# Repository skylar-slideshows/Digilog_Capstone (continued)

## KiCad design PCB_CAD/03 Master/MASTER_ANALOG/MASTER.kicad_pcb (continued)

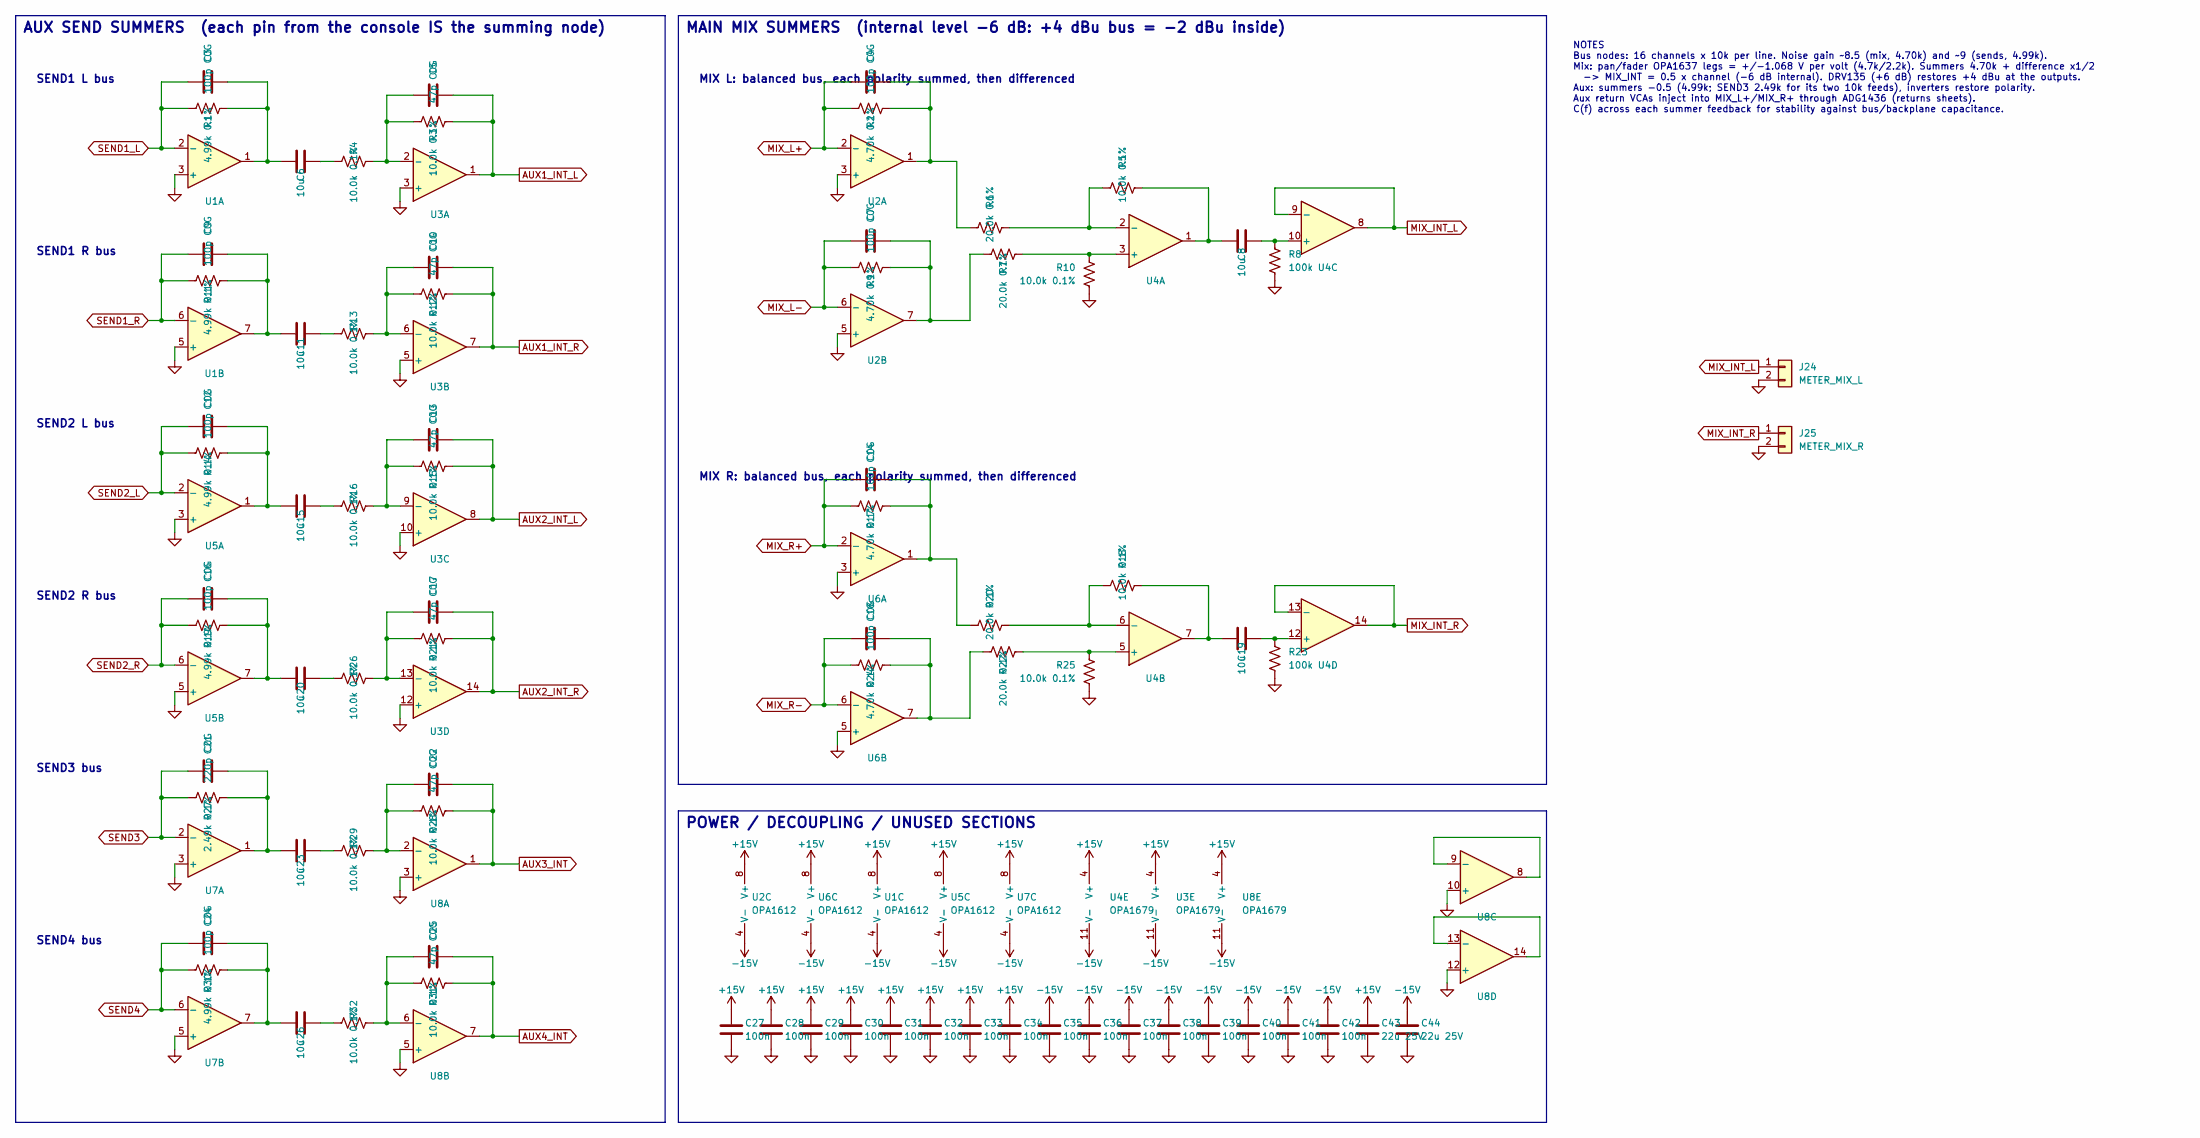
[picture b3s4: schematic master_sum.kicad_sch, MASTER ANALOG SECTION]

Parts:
C3, C4, C7, C9, C12, C14, C16, C18, C24: 100p C0G; C_0603_1608Metric; LCSC C14665
C5, C10, C13, C17, C22, C25: 47p C0G; C_0603_1608Metric; LCSC C105622
C6, C8, C11, C15, C19, C20, C23, C26: 10u; CP_Elec_6.3x5.4_Nichicon; LCSC C340735
C21: 220p C0G; C_0603_1608Metric; LCSC C694226
C27, C28, C29, C30, C31, C32, C33, C34, C35, C36, C37, C38, C39, C40, C41, C42: 100n; C_0603_1608Metric; LCSC C1590
C43, C44: 22u 25V; C_1210_3225Metric; LCSC C21397
J24: METER_MIX_L; PinHeader_1x02_P2.54mm_Vertical; LCSC dnp
J25: METER_MIX_R; PinHeader_1x02_P2.54mm_Vertical; LCSC dnp
R1, R11, R14, R19, R30: 4.99k 0.1%; R_0603_1608Metric; LCSC C190614
R2, R9, R17, R24: 4.70k 0.1%; R_0603_1608Metric; LCSC C328429
R3, R4, R5, R10, R12, R13, R15, R16, R18, R21, R25, R26, R28, R29, R31, R32: 10.0k 0.1%; R_0603_1608Metric; LCSC C95204
R6, R7, R20, R22: 20.0k 0.1%; R_0603_1608Metric; LCSC C190611
R8, R23: 100k; R_0603_1608Metric; LCSC C122538
R27: 2.49k 0.1%; R_0603_1608Metric; LCSC C319797
U1, U2, U5, U6, U7: OPA1612; SOIC-8_3.9x4.9mm_P1.27mm; LCSC C94590
U3, U4, U8: OPA1679; TSSOP-14_4.4x5mm_P0.65mm; LCSC C2057264

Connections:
+15V: C27.1, C28.1, C29.1, C30.1, C31.1, C32.1, C33.1, C34.1, C43.1, U1.8 (V+), U2.8 (V+), U3.4 (V+), U4.4 (V+), U5.8 (V+), U6.8 (V+), U7.8 (V+), U8.4 (V+); also elsewhere on the board
-15V: C35.1, C36.1, C37.1, C38.1, C39.1, C40.1, C41.1, C42.1, C44.1, U1.4 (V-), U2.4 (V-), U3.11 (V-), U4.11 (V-), U5.4 (V-), U6.4 (V-), U7.4 (V-), U8.11 (V-); also elsewhere on the board
AUX1_INT_L: C5.2, R3.2, U3.1; also elsewhere on the board
AUX1_INT_R: C10.2, R12.2, U3.7; also elsewhere on the board
AUX2_INT_L: C13.2, R15.2, U3.8; also elsewhere on the board
AUX2_INT_R: C17.2, R21.2, U3.14; also elsewhere on the board
AUX3_INT: C22.2, R28.2, U8.1; also elsewhere on the board
AUX4_INT: C25.2, R31.2, U8.7; also elsewhere on the board
GND: C27.2, C28.2, C29.2, C30.2, C31.2, C32.2, C33.2, C34.2, C35.2, C36.2, C37.2, C38.2, C39.2, C40.2, C41.2, C42.2, C43.2, C44.2, J24.2, J25.2, R8.2, R10.2, R23.2, R25.2, U1.3 (+), U1.5 (+), U2.3 (+), U2.5 (+), U3.3 (+), U3.5 (+), U3.10 (+), U3.12 (+), U5.3 (+), U5.5 (+), U6.3 (+), U6.5 (+), U7.3 (+), U7.5 (+), U8.3 (+), U8.5 (+), U8.10 (+), U8.12 (+); also elsewhere on the board
MIX_INT_L: J24.1, U4.8, U4.9 (-); also elsewhere on the board
MIX_INT_R: J25.1, U4.13 (-), U4.14; also elsewhere on the board
MIX_L+: C4.1, R2.1, U2.2 (-); also elsewhere on the board
MIX_L-: C7.1, R9.1, U2.6 (-); also elsewhere on the board
MIX_R+: C14.1, R17.1, U6.2 (-); also elsewhere on the board
MIX_R-: C18.1, R24.1, U6.6 (-); also elsewhere on the board
unnamed: C3.2, C6.1, R1.2, U1.1
unnamed: C4.2, R2.2, R6.1, U2.1
unnamed: C6.2, R4.1
unnamed: C7.2, R7.1, R9.2, U2.7
unnamed: C8.1, R5.2, U4.1
unnamed: C9.2, C11.1, R11.2, U1.7
unnamed: C11.2, R13.1
unnamed: C12.2, C15.1, R14.2, U5.1
unnamed: C14.2, R17.2, R20.1, U6.1
unnamed: C15.2, R16.1
unnamed: C16.2, C20.1, R19.2, U5.7
unnamed: C18.2, R22.1, R24.2, U6.7
unnamed: C19.1, R18.2, U4.7
unnamed: C20.2, R26.1
unnamed: C21.2, C23.1, R27.2, U7.1
unnamed: C23.2, R29.1
unnamed: C24.2, C26.1, R30.2, U7.7
unnamed: C26.2, R32.1
unnamed: C5.1, R3.1, R4.2, U3.2 (-)
unnamed: C10.1, R12.1, R13.2, U3.6 (-)
unnamed: C13.1, R15.1, R16.2, U3.9 (-)
unnamed: C17.1, R21.1, R26.2, U3.13 (-)
unnamed: R7.2, R10.1, U4.3 (+)
unnamed: R5.1, R6.2, U4.2 (-)
unnamed: R22.2, R25.1, U4.5 (+)
unnamed: R18.1, R20.2, U4.6 (-)
unnamed: C8.2, R8.1, U4.10 (+)
unnamed: C19.2, R23.1, U4.12 (+)
unnamed: C22.1, R28.1, R29.2, U8.2 (-)
unnamed: C25.1, R31.1, R32.2, U8.6 (-)
unnamed: U8.8, U8.9 (-)
unnamed: U8.13 (-), U8.14
SEND1_L: C3.1, R1.1, U1.2 (-); also elsewhere on the board
SEND1_R: C9.1, R11.1, U1.6 (-); also elsewhere on the board
SEND2_L: C12.1, R14.1, U5.2 (-); also elsewhere on the board
SEND2_R: C16.1, R19.1, U5.6 (-); also elsewhere on the board
SEND3: C21.1, R27.1, U7.2 (-); also elsewhere on the board
SEND4: C24.1, R30.1, U7.6 (-); also elsewhere on the board

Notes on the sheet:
SEND3 bus
SEND2 R bus
SEND1 L bus
MIX L: balanced bus, each polarity summed, then differenced
SEND1 R bus
MAIN MIX SUMMERS (internal level -6 dB: +4 dBu bus = -2 dBu inside)
NOTES Bus nodes: 16 channels x 10k per line. Noise gain ~8.5 (mix, 4.70k) and ~9 (sends, 4.99k). Mix: pan/fader OPA1637 legs = +/-1.068 V per volt (4.7k/2.2k). Summers 4.70k + difference x1/2 -> MIX_INT = 0.5 x channel (-6 dB internal). DRV135 (+6 dB) restores +4 dBu at the outputs. Aux: summers -0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
SEND4 bus
AUX SEND SUMMERS (each pin from the console IS the summing node)
MIX R: balanced bus, each polarity summed, then differenced
SEND2 L bus
POWER / DECOUPLING / UNUSED SECTIONS

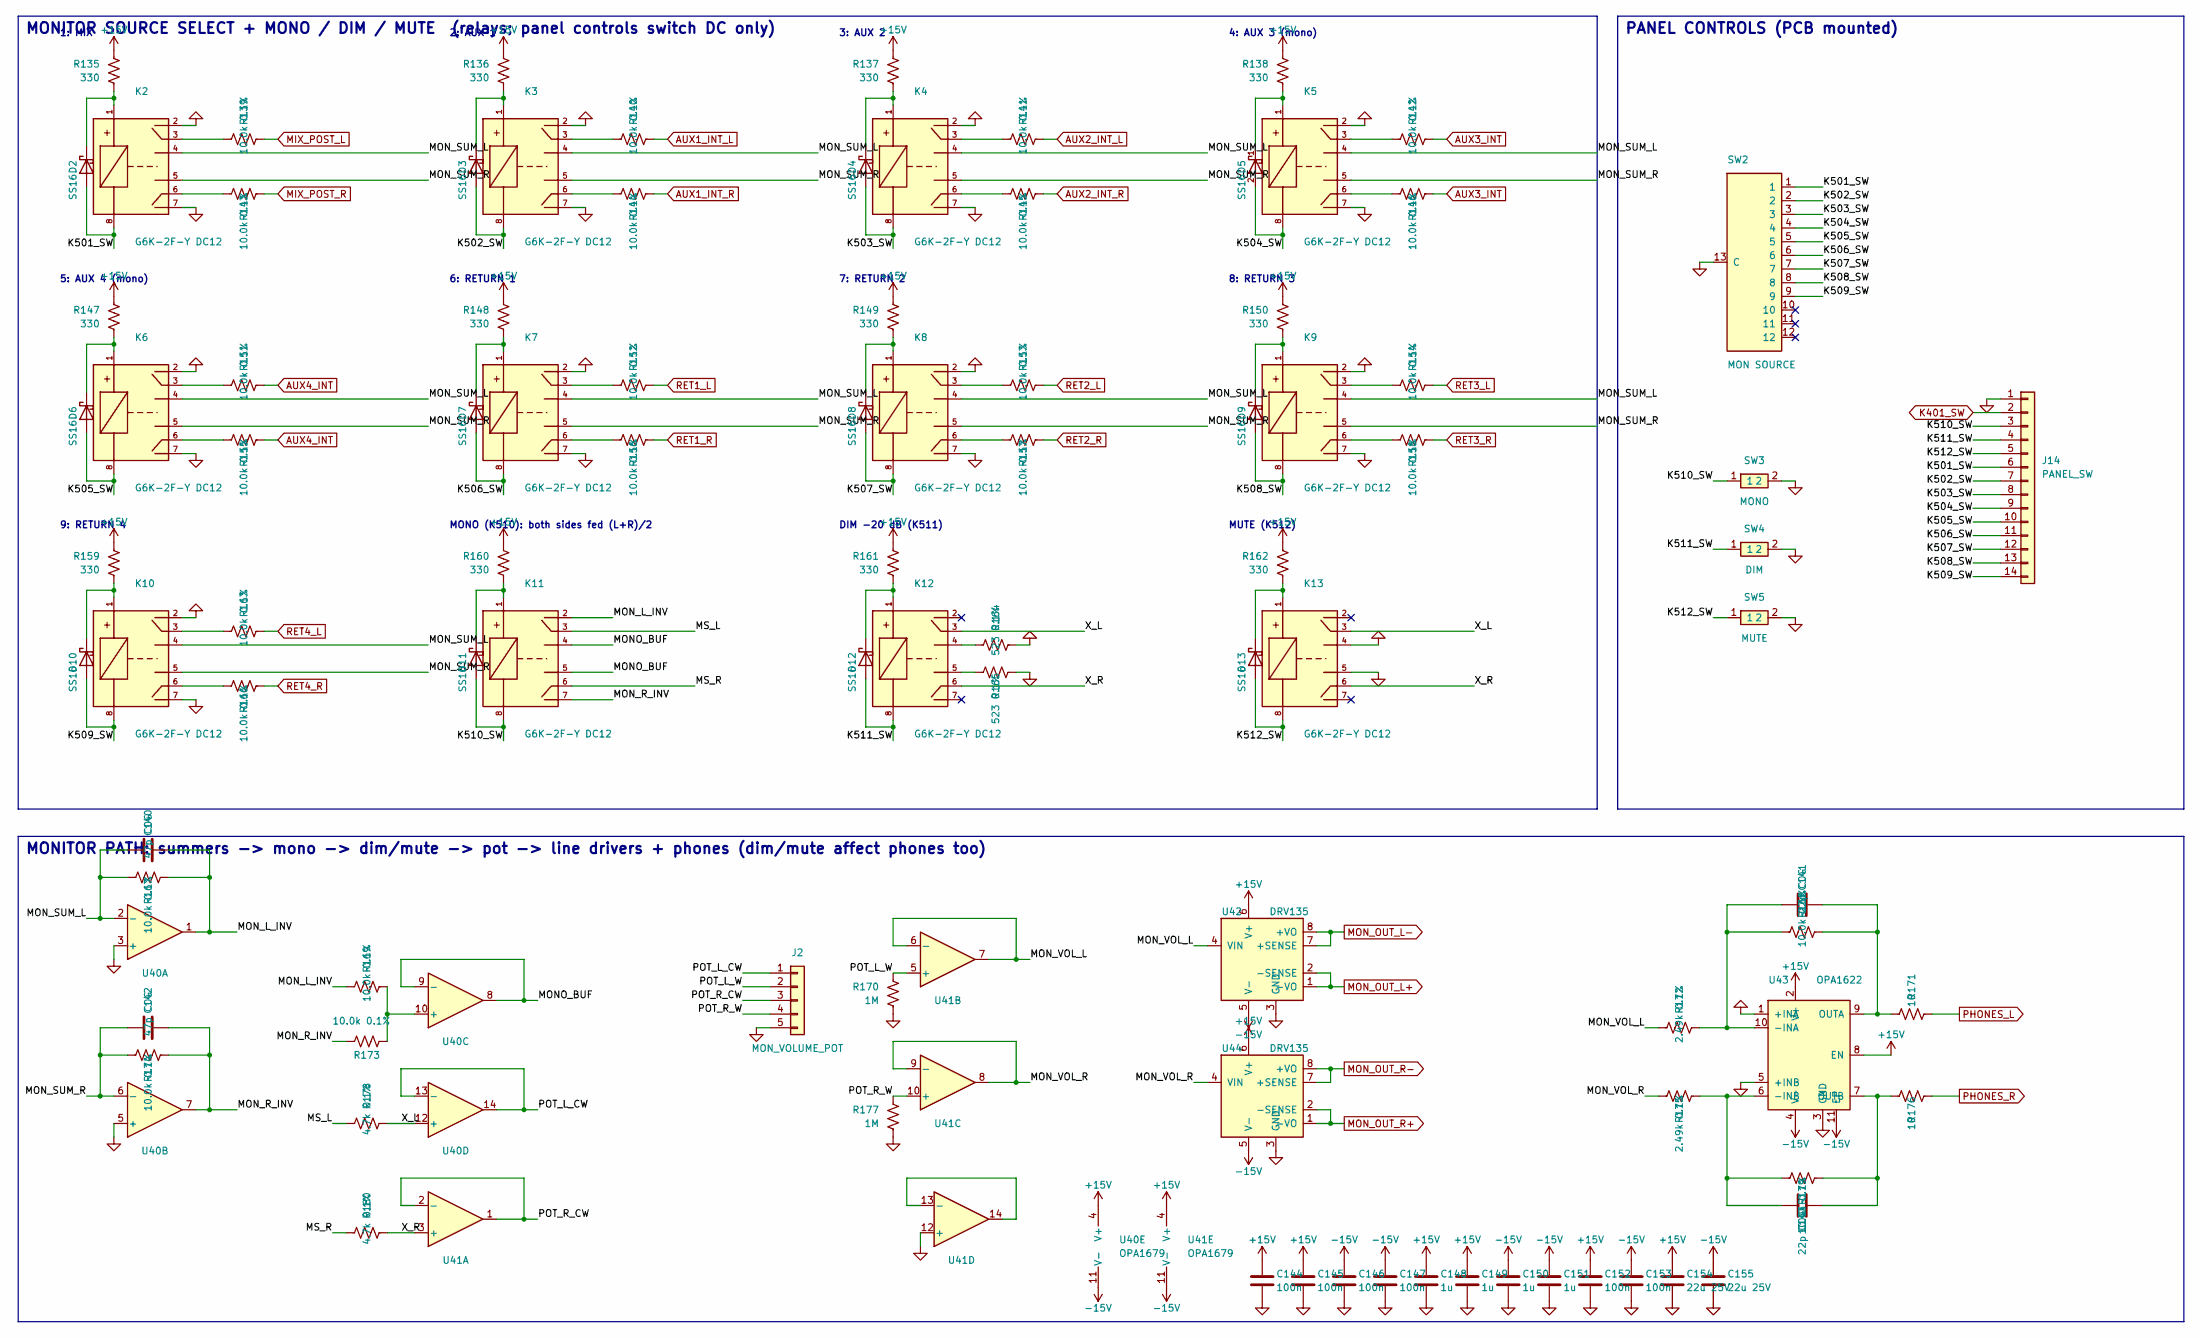
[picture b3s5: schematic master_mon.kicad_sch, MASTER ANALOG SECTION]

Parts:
C140, C142: 47p C0G; C_0603_1608Metric; LCSC C105622
C141, C143: 22p C0G; C_0603_1608Metric; LCSC C105620
C144, C145, C146, C147, C152, C153: 100n; C_0603_1608Metric; LCSC C1590
C148, C149, C150, C151: 1u; C_0603_1608Metric; LCSC C15849
C154, C155: 22u 25V; C_1210_3225Metric; LCSC C21397
D2, D3, D4, D5, D6, D7, D8, D9, D10, D11, D12, D13: SS16; D_SMA; LCSC C2481
J2: MON_VOLUME_POT; PinHeader_1x05_P2.54mm_Vertical; LCSC dnp
J14: PANEL_SW; PinHeader_1x14_P2.54mm_Vertical; LCSC dnp
K2, K3, K4, K5, K6, K7, K8, K9, K10, K11, K12, K13: G6K-2F-Y DC12; Relay_DPDT_Omron_G6K-2F-Y; LCSC C397194
R135, R136, R137, R138, R147, R148, R149, R150, R159, R160, R161, R162: 330; R_1206_3216Metric; LCSC C17930
R139, R140, R141, R142, R143, R144, R145, R146, R151, R152, R153, R154, R155, R156, R157, R158, R163, R166, R167, R168, R169, R173, R174, R179: 10.0k 0.1%; R_0603_1608Metric; LCSC C95204
R164, R165: 523 0.1%; R_0603_1608Metric; LCSC C861461
R170, R177: 1M; R_0603_1608Metric; LCSC C234360
R171, R176: 10; R_0805_2012Metric; LCSC C136903
R172, R175: 2.49k 0.1%; R_0603_1608Metric; LCSC C319797
R178, R180: 4.7k 0.1%; R_0603_1608Metric; LCSC C328429
SW2: MON SOURCE; PinHeader_1x02_P2.54mm_Vertical; LCSC dnp
SW3: MONO; PinHeader_1x02_P2.54mm_Vertical; LCSC dnp
SW4: DIM; PinHeader_1x02_P2.54mm_Vertical; LCSC dnp
SW5: MUTE; PinHeader_1x02_P2.54mm_Vertical; LCSC dnp
U40, U41: OPA1679; TSSOP-14_4.4x5mm_P0.65mm; LCSC C2057264
U42, U44: DRV135; SOIC-8_3.9x4.9mm_P1.27mm; LCSC C544663
U43: OPA1622; Texas_S-PVSON-N10_ThermalVias; LCSC C2876559

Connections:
+15V: C144.1, C145.1, C148.1, C149.1, C152.1, C154.1, R135.1, R136.1, R137.1, R138.1, R147.1, R148.1, R149.1, R150.1, R159.1, R160.1, R161.1, R162.1, U40.4 (V+), U41.4 (V+), U42.6 (V+), U43.2 (V+), U43.8 (EN), U44.6 (V+); also elsewhere on the board
-15V: C146.1, C147.1, C150.1, C151.1, C153.1, C155.1, U40.11 (V-), U41.11 (V-), U42.5 (V-), U43.4 (V-), U43.11 (EP), U44.5 (V-); also elsewhere on the board
/MONITOR/K501_SW: D2.2 (A), J14.6, K2.8 (-), SW2.1
/MONITOR/K502_SW: D3.2 (A), J14.7, K3.8 (-), SW2.2
/MONITOR/K503_SW: D4.2 (A), J14.8, K4.8 (-), SW2.3
/MONITOR/K504_SW: D5.2 (A), J14.9, K5.8 (-), SW2.4
/MONITOR/K505_SW: D6.2 (A), J14.10, K6.8 (-), SW2.5
/MONITOR/K506_SW: D7.2 (A), J14.11, K7.8 (-), SW2.6
/MONITOR/K507_SW: D8.2 (A), J14.12, K8.8 (-), SW2.7
/MONITOR/K508_SW: D9.2 (A), J14.13, K9.8 (-), SW2.8
/MONITOR/K509_SW: D10.2 (A), J14.14, K10.8 (-), SW2.9
/MONITOR/K510_SW: D11.2 (A), J14.3, K11.8 (-), SW3.1
/MONITOR/K511_SW: D12.2 (A), J14.4, K12.8 (-), SW4.1
/MONITOR/K512_SW: D13.2 (A), J14.5, K13.8 (-), SW5.1
/MONITOR/MONO_BUF: K11.4 (NO1), K11.5 (NO2), U40.8, U40.9 (-)
/MONITOR/MON_L_INV: C140.2, K11.2 (NC1), R167.2, R169.1, U40.1
/MONITOR/MON_R_INV: C142.2, K11.7 (NC2), R173.1, R174.2, U40.7
/MONITOR/MON_SUM_L: C140.1, K2.4 (NO1), K3.4 (NO1), K4.4 (NO1), K5.4 (NO1), K6.4 (NO1), K7.4 (NO1), K8.4 (NO1), K9.4 (NO1), K10.4 (NO1), R167.1, U40.2 (-)
/MONITOR/MON_SUM_R: C142.1, K2.5 (NO2), K3.5 (NO2), K4.5 (NO2), K5.5 (NO2), K6.5 (NO2), K7.5 (NO2), K8.5 (NO2), K9.5 (NO2), K10.5 (NO2), R174.1, U40.6 (-)
/MONITOR/MON_VOL_L: R172.1, U41.6 (-), U41.7, U42.4 (VIN)
/MONITOR/MON_VOL_R: R175.1, U41.8, U41.9 (-), U44.4 (VIN)
/MONITOR/MS_L: K11.3 (COM1), R178.1
/MONITOR/MS_R: K11.6 (COM2), R180.1
/MONITOR/POT_L_CW: J2.1, U40.13 (-), U40.14
/MONITOR/POT_L_W: J2.2, R170.1, U41.5 (+)
/MONITOR/POT_R_CW: J2.3, U41.1, U41.2 (-)
/MONITOR/POT_R_W: J2.4, R177.1, U41.10 (+)
/MONITOR/X_L: K12.3 (COM1), K13.3 (COM1), R178.2, U40.12 (+)
/MONITOR/X_R: K12.6 (COM2), K13.6 (COM2), R180.2, U41.3 (+)
AUX1_INT_L: R140.2; also elsewhere on the board
AUX1_INT_R: R144.2; also elsewhere on the board
AUX2_INT_L: R141.2; also elsewhere on the board
AUX2_INT_R: R145.2; also elsewhere on the board
AUX3_INT: R142.2, R146.2; also elsewhere on the board
AUX4_INT: R151.2, R155.2; also elsewhere on the board
GND: C144.2, C145.2, C146.2, C147.2, C148.2, C149.2, C150.2, C151.2, C152.2, C153.2, C154.2, C155.2, J2.5, J14.1, K2.2 (NC1), K2.7 (NC2), K3.2 (NC1), K3.7 (NC2), K4.2 (NC1), K4.7 (NC2), K5.2 (NC1), K5.7 (NC2), K6.2 (NC1), K6.7 (NC2), K7.2 (NC1), K7.7 (NC2), K8.2 (NC1), K8.7 (NC2), K9.2 (NC1), K9.7 (NC2), K10.2 (NC1), K10.7 (NC2), K13.4 (NO1), K13.5 (NO2), R164.2, R165.2, R170.2, R177.2, SW2.13 (C), SW3.2, SW4.2, SW5.2, U40.3 (+), U40.5 (+), U41.12 (+), U42.3 (GND), U43.1 (+INA), U43.3 (GND), U43.5 (+INB), U44.3 (GND); also elsewhere on the board
K401_SW: J14.2; also elsewhere on the board
MIX_POST_L: R139.2; also elsewhere on the board
MIX_POST_R: R143.2; also elsewhere on the board
MON_OUT_L+: U42.1 (-VO), U42.2 (-SENSE); also elsewhere on the board
MON_OUT_L-: U42.7 (+SENSE), U42.8 (+VO); also elsewhere on the board
MON_OUT_R+: U44.1 (-VO), U44.2 (-SENSE); also elsewhere on the board
MON_OUT_R-: U44.7 (+SENSE), U44.8 (+VO); also elsewhere on the board
unnamed: D2.1 (K), K2.1 (+), R135.2
unnamed: D3.1 (K), K3.1 (+), R136.2
unnamed: D4.1 (K), K4.1 (+), R137.2
unnamed: D5.1 (K), K5.1 (+), R138.2
unnamed: D6.1 (K), K6.1 (+), R147.2
unnamed: D7.1 (K), K7.1 (+), R148.2
unnamed: D8.1 (K), K8.1 (+), R149.2
unnamed: D9.1 (K), K9.1 (+), R150.2
unnamed: D10.1 (K), K10.1 (+), R159.2
unnamed: D11.1 (K), K11.1 (+), R160.2
unnamed: D12.1 (K), K12.1 (+), R161.2
unnamed: D13.1 (K), K13.1 (+), R162.2
unnamed: K2.3 (COM1), R139.1
unnamed: K2.6 (COM2), R143.1
unnamed: K3.3 (COM1), R140.1
unnamed: K3.6 (COM2), R144.1
unnamed: K4.3 (COM1), R141.1
unnamed: K4.6 (COM2), R145.1
unnamed: K5.3 (COM1), R142.1
unnamed: K5.6 (COM2), R146.1
unnamed: K6.3 (COM1), R151.1
unnamed: K6.6 (COM2), R155.1
unnamed: K7.3 (COM1), R152.1
unnamed: K7.6 (COM2), R156.1
unnamed: K8.3 (COM1), R153.1
unnamed: K8.6 (COM2), R157.1
unnamed: K9.3 (COM1), R154.1
unnamed: K9.6 (COM2), R158.1
unnamed: K10.3 (COM1), R163.1
unnamed: K10.6 (COM2), R166.1
unnamed: K12.4 (NO1), R164.1
unnamed: K12.5 (NO2), R165.1
unnamed: R169.2, R173.2, U40.10 (+)
unnamed: U41.13 (-), U41.14
unnamed: C141.1, R168.1, R172.2, U43.10 (-INA)
unnamed: C143.1, R175.2, R179.1, U43.6 (-INB)
unnamed: C141.2, R168.2, R171.1, U43.9 (OUTA)
unnamed: C143.2, R176.1, R179.2, U43.7 (OUTB)
PHONES_L: R171.2; also elsewhere on the board
PHONES_R: R176.2; also elsewhere on the board
RET1_L: R152.2; also elsewhere on the board
RET1_R: R156.2; also elsewhere on the board
RET2_L: R153.2; also elsewhere on the board
RET2_R: R157.2; also elsewhere on the board
RET3_L: R154.2; also elsewhere on the board
RET3_R: R158.2; also elsewhere on the board
RET4_L: R163.2; also elsewhere on the board
RET4_R: R166.2; also elsewhere on the board

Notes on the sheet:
8: RETURN 3
5: AUX 4 (mono)
MONITOR PATH: summers -> mono -> dim/mute -> pot -> line drivers + phones (dim/mute affect phones too)
1: MIX
4: AUX 3 (mono)
DIM -20 dB (K511)
3: AUX 2
PANEL CONTROLS (PCB mounted)
MONITOR SOURCE SELECT + MONO / DIM / MUTE (relays; panel controls switch DC only)
2: AUX 1
7: RETURN 2
6: RETURN 1
9: RETURN 4
MONO (K510): both sides fed (L+R)/2
MUTE (K512)

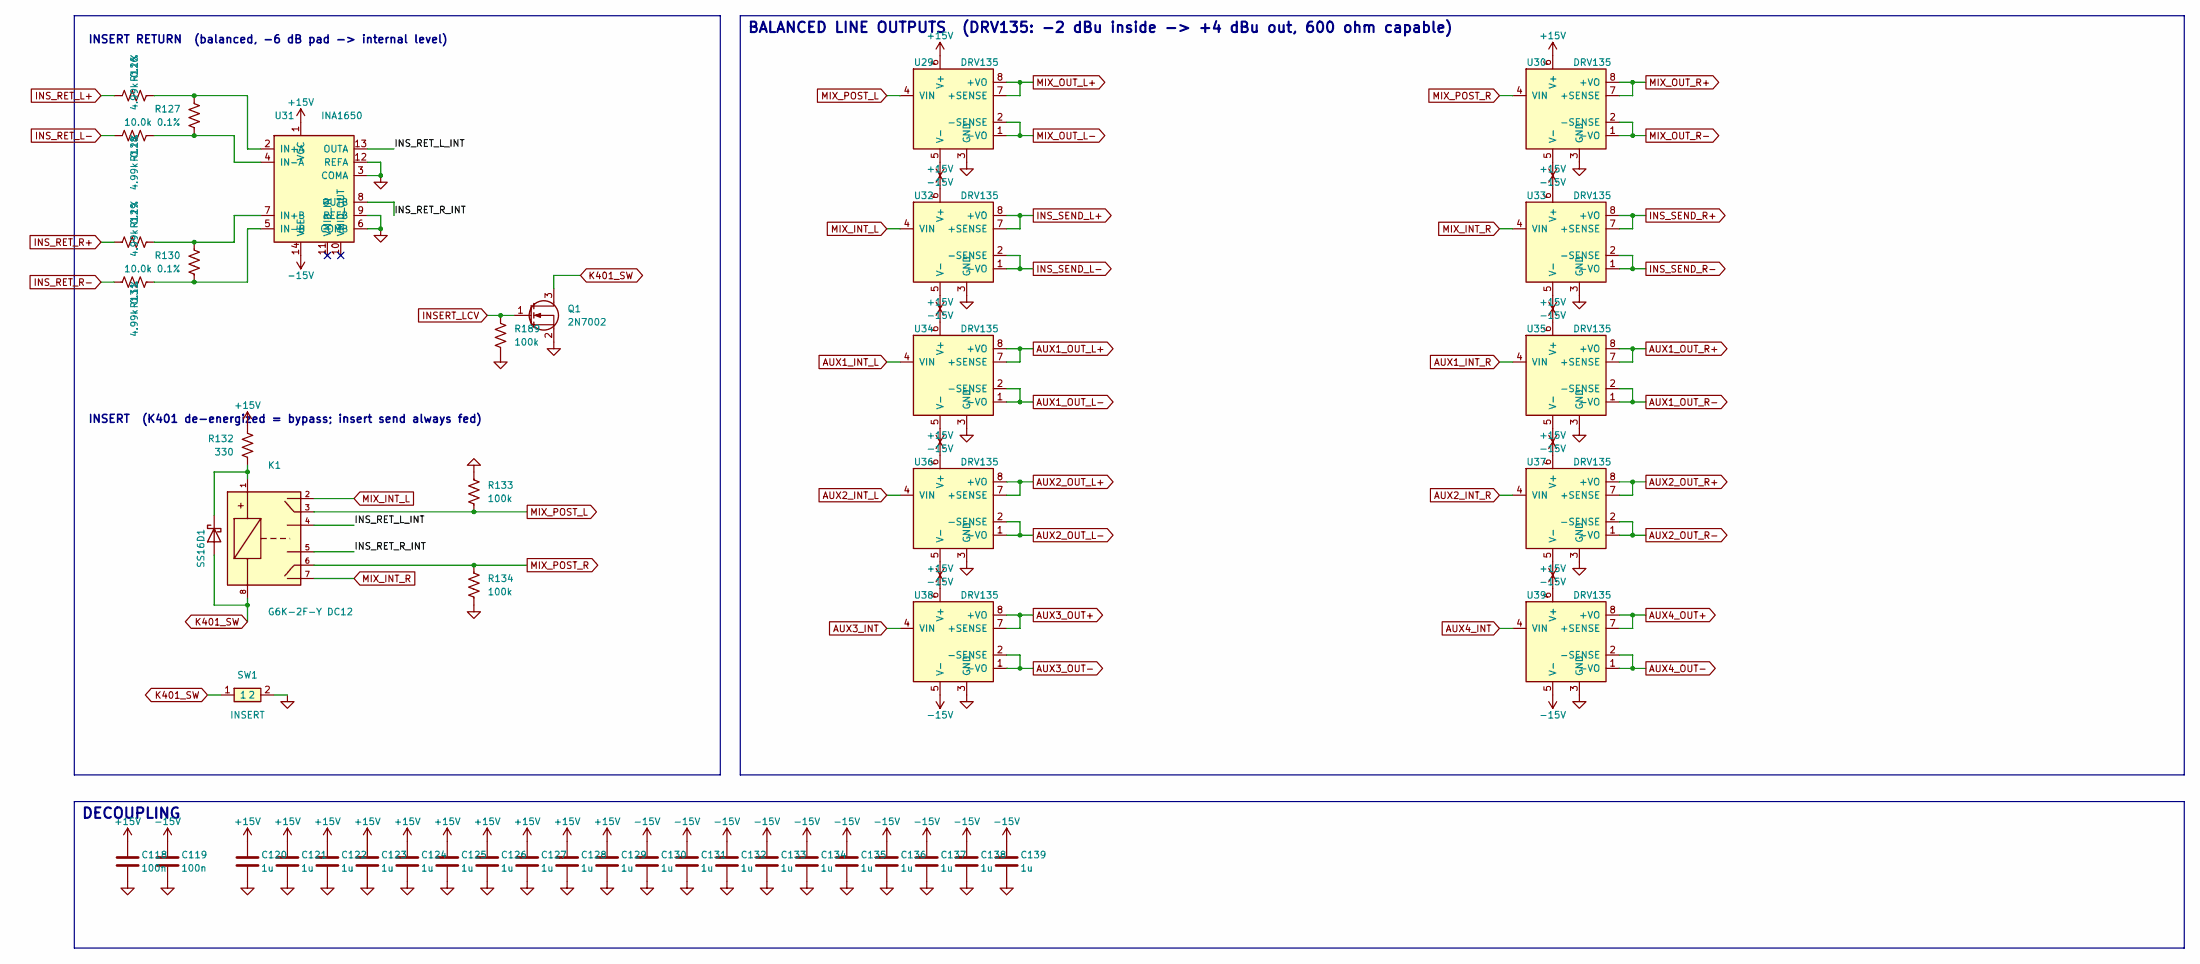
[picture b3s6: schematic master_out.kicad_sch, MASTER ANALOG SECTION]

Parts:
C118, C119: 100n; C_0603_1608Metric; LCSC C1590
C120, C121, C122, C123, C124, C125, C126, C127, C128, C129, C130, C131, C132, C133, C134, C135, C136, C137, C138, C139: 1u; C_0603_1608Metric; LCSC C15849
D1: SS16; D_SMA; LCSC C2481
K1: G6K-2F-Y DC12; Relay_DPDT_Omron_G6K-2F-Y; LCSC C397194
Q1: 2N7002; SOT-23; LCSC C8545
R126, R128, R129, R131: 4.99k 0.1%; R_0603_1608Metric; LCSC C190614
R127, R130: 10.0k 0.1%; R_0603_1608Metric; LCSC C95204
R132: 330; R_1206_3216Metric; LCSC C17930
R133, R134, R189: 100k; R_0603_1608Metric; LCSC C122538
SW1: INSERT; PinHeader_1x02_P2.54mm_Vertical; LCSC dnp
U29, U30, U32, U33, U34, U35, U36, U37, U38, U39: DRV135; SOIC-8_3.9x4.9mm_P1.27mm; LCSC C544663
U31: INA1650; TSSOP-14_4.4x5mm_P0.65mm; LCSC C553130

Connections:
+15V: C118.1, C120.1, C121.1, C122.1, C123.1, C124.1, C125.1, C126.1, C127.1, C128.1, C129.1, R132.1, U29.6 (V+), U30.6 (V+), U31.1 (VCC), U32.6 (V+), U33.6 (V+), U34.6 (V+), U35.6 (V+), U36.6 (V+), U37.6 (V+), U38.6 (V+), U39.6 (V+); also elsewhere on the board
-15V: C119.1, C130.1, C131.1, C132.1, C133.1, C134.1, C135.1, C136.1, C137.1, C138.1, C139.1, U29.5 (V-), U30.5 (V-), U31.14 (VEE), U32.5 (V-), U33.5 (V-), U34.5 (V-), U35.5 (V-), U36.5 (V-), U37.5 (V-), U38.5 (V-), U39.5 (V-); also elsewhere on the board
/INSERT & OUTPUTS/INS_RET_L_INT: K1.4 (NO1), U31.13 (OUTA)
/INSERT & OUTPUTS/INS_RET_R_INT: K1.5 (NO2), U31.8 (OUTB)
AUX1_INT_L: U34.4 (VIN); also elsewhere on the board
AUX1_INT_R: U35.4 (VIN); also elsewhere on the board
AUX1_OUT_L+: U34.7 (+SENSE), U34.8 (+VO); also elsewhere on the board
AUX1_OUT_L-: U34.1 (-VO), U34.2 (-SENSE); also elsewhere on the board
AUX1_OUT_R+: U35.7 (+SENSE), U35.8 (+VO); also elsewhere on the board
AUX1_OUT_R-: U35.1 (-VO), U35.2 (-SENSE); also elsewhere on the board
AUX2_INT_L: U36.4 (VIN); also elsewhere on the board
AUX2_INT_R: U37.4 (VIN); also elsewhere on the board
AUX2_OUT_L+: U36.7 (+SENSE), U36.8 (+VO); also elsewhere on the board
AUX2_OUT_L-: U36.1 (-VO), U36.2 (-SENSE); also elsewhere on the board
AUX2_OUT_R+: U37.7 (+SENSE), U37.8 (+VO); also elsewhere on the board
AUX2_OUT_R-: U37.1 (-VO), U37.2 (-SENSE); also elsewhere on the board
AUX3_INT: U38.4 (VIN); also elsewhere on the board
AUX3_OUT+: U38.7 (+SENSE), U38.8 (+VO); also elsewhere on the board
AUX3_OUT-: U38.1 (-VO), U38.2 (-SENSE); also elsewhere on the board
AUX4_INT: U39.4 (VIN); also elsewhere on the board
AUX4_OUT+: U39.7 (+SENSE), U39.8 (+VO); also elsewhere on the board
AUX4_OUT-: U39.1 (-VO), U39.2 (-SENSE); also elsewhere on the board
GND: C118.2, C119.2, C120.2, C121.2, C122.2, C123.2, C124.2, C125.2, C126.2, C127.2, C128.2, C129.2, C130.2, C131.2, C132.2, C133.2, C134.2, C135.2, C136.2, C137.2, C138.2, C139.2, Q1.2 (S), R133.1, R134.2, R189.2, SW1.2, U29.3 (GND), U30.3 (GND), U31.3 (COMA), U31.6 (COMB), U31.9 (REFB), U31.12 (REFA), U32.3 (GND), U33.3 (GND), U34.3 (GND), U35.3 (GND), U36.3 (GND), U37.3 (GND), U38.3 (GND), U39.3 (GND); also elsewhere on the board
INSERT_LCV: Q1.1 (G), R189.1; also elsewhere on the board
INS_RET_L+: R126.1; also elsewhere on the board
INS_RET_L-: R128.1; also elsewhere on the board
INS_RET_R+: R129.1; also elsewhere on the board
INS_RET_R-: R131.1; also elsewhere on the board
INS_SEND_L+: U32.7 (+SENSE), U32.8 (+VO); also elsewhere on the board
INS_SEND_L-: U32.1 (-VO), U32.2 (-SENSE); also elsewhere on the board
INS_SEND_R+: U33.7 (+SENSE), U33.8 (+VO); also elsewhere on the board
INS_SEND_R-: U33.1 (-VO), U33.2 (-SENSE); also elsewhere on the board
K401_SW: D1.2 (A), K1.8 (-), Q1.3 (D), SW1.1; also elsewhere on the board
MIX_INT_L: K1.2 (NC1), U32.4 (VIN); also elsewhere on the board
MIX_INT_R: K1.7 (NC2), U33.4 (VIN); also elsewhere on the board
MIX_OUT_L+: U29.7 (+SENSE), U29.8 (+VO); also elsewhere on the board
MIX_OUT_L-: U29.1 (-VO), U29.2 (-SENSE); also elsewhere on the board
MIX_OUT_R+: U30.7 (+SENSE), U30.8 (+VO); also elsewhere on the board
MIX_OUT_R-: U30.1 (-VO), U30.2 (-SENSE); also elsewhere on the board
MIX_POST_L: K1.3 (COM1), R133.2, U29.4 (VIN); also elsewhere on the board
MIX_POST_R: K1.6 (COM2), R134.1, U30.4 (VIN); also elsewhere on the board
unnamed: D1.1 (K), K1.1 (+), R132.2
unnamed: R126.2, R127.1, U31.2 (IN+A)
unnamed: R129.2, R130.1, U31.7 (IN+B)
unnamed: R127.2, R128.2, U31.4 (IN-A)
unnamed: R130.2, R131.2, U31.5 (IN-B)

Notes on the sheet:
INSERT RETURN (balanced, -6 dB pad -> internal level)
INSERT (K401 de-energized = bypass; insert send always fed)
DECOUPLING
BALANCED LINE OUTPUTS (DRV135: -2 dBu inside -> +4 dBu out, 600 ohm capable)

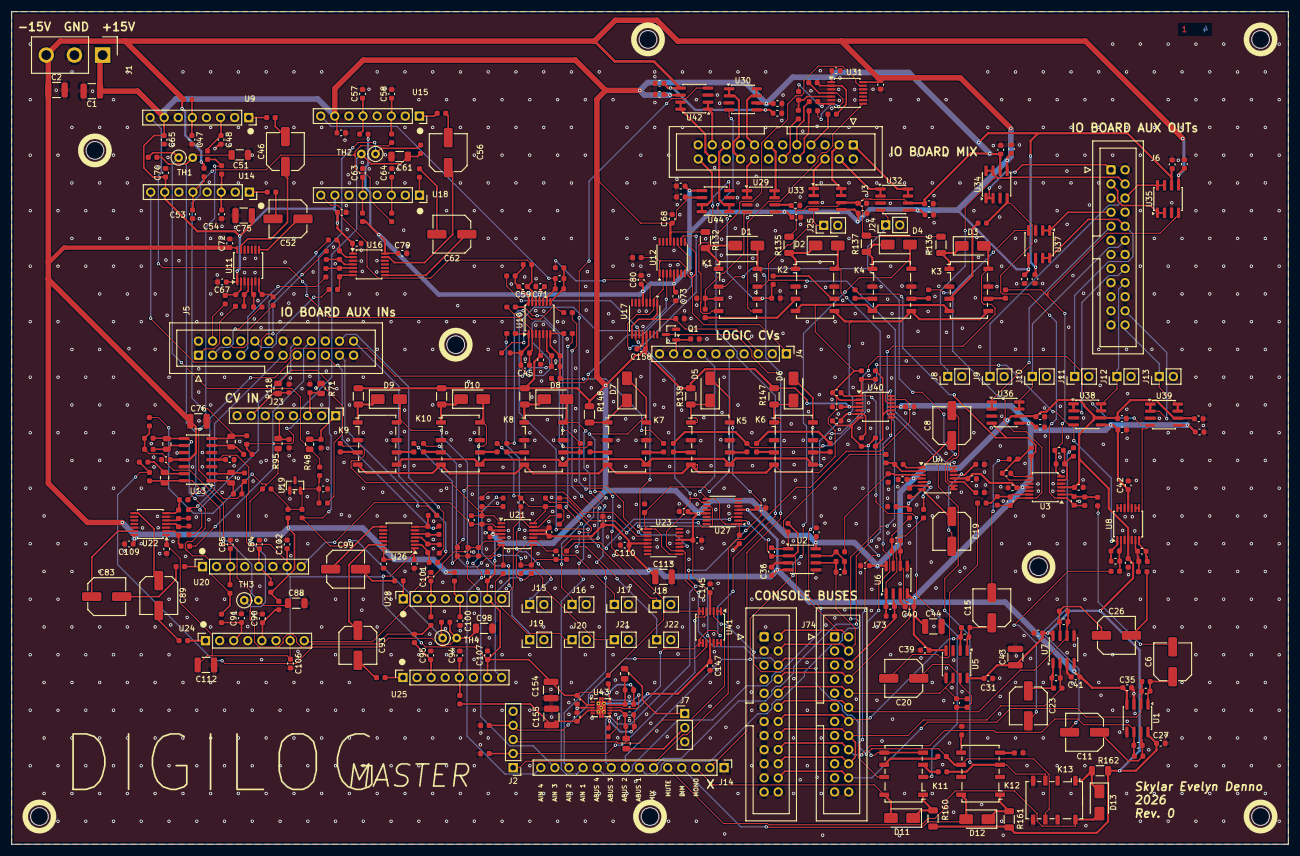
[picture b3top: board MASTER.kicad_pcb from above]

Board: 4 copper layers, 230.0 x 150.0 mm, 457 parts (0 on the bottom side), 288 nets.

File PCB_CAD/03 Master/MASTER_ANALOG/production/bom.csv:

Designator,Footprint,Quantity,Value,LCSC Part #
"C1, C112, C113, C154, C155, C2, C43, C44, C75, C76",1210,10,22u 25V,C21397
"C10, C13, C140, C142, C17, C22, C25, C5",0603,8,47p C0G,C105622
"C100, C102, C103, C104, C105, C106, C107, C108, C109, C110, C111, C114, C115, C116, C117, C118, C119, C144, C145, C146, C147, C152, C153, C156, C157, C158, C27, C28, C29, C30, C31, C32, C33, C34, C35, C36, C37, C38, C39, C40, C41, C42, C47, C53, C57, C63, C65, C66, C67, C68, C69, C70, C71, C72, C73, C74, C77, C78, C79, C80, C81, C84, C90, C94",0603,64,100n,C1590
"C101, C48, C54, C58, C64, C85, C91, C95",0603,8,2.2n C0G,C107043
"C11, C15, C19, C20, C23, C26, C46, C52, C56, C6, C62, C8, C83, C89, C93, C99",CP_Elec_6.3x5.4_Nichicon,16,10u,C340735
"C12, C14, C16, C18, C24, C3, C4, C7, C9",0603,9,100p C0G,C14665
"C120, C121, C122, C123, C124, C125, C126, C127, C128, C129, C130, C131, C132, C133, C134, C135, C136, C137, C138, C139, C148, C149, C150, C151",0603,24,1u,C15849
"C141, C143, C45, C49, C55, C59, C82, C86, C92, C96",0603,10,22p C0G,C105620
C21,0603,1,220p C0G,C694226
"C50, C60, C87, C97",0805,4,8.2n C0G,C296107
"C51, C61, C88, C98",1206,4,22n C0G,C105982
"D1, D10, D11, D12, D13, D2, D3, D4, D5, D6, D7, D8, D9",D_SMA,13,SS16,C2481
J1,Samtec_HPM-03-05-x-S_Straight_1x03_Pitch5.08mm,1,POWER,dnp
J10,PinHeader_1x02_P2.54mm_Vertical,1,METER_AUX2L,dnp
J11,PinHeader_1x02_P2.54mm_Vertical,1,METER_AUX2R,dnp
J12,PinHeader_1x02_P2.54mm_Vertical,1,METER_AUX3,dnp
J13,PinHeader_1x02_P2.54mm_Vertical,1,METER_AUX4,dnp
J14,PinHeader_1x14_P2.54mm_Vertical,1,PANEL_SW,dnp
J15,PinHeader_1x02_P2.54mm_Vertical,1,METER_RET1L,dnp
J16,PinHeader_1x02_P2.54mm_Vertical,1,METER_RET1R,dnp
J17,PinHeader_1x02_P2.54mm_Vertical,1,METER_RET2L,dnp
J18,PinHeader_1x02_P2.54mm_Vertical,1,METER_RET2R,dnp
J19,PinHeader_1x02_P2.54mm_Vertical,1,METER_RET3L,dnp
J2,PinHeader_1x05_P2.54mm_Vertical,1,MON_VOLUME_POT,dnp
J20,PinHeader_1x02_P2.54mm_Vertical,1,METER_RET3R,dnp
J21,PinHeader_1x02_P2.54mm_Vertical,1,METER_RET4L,dnp
J22,PinHeader_1x02_P2.54mm_Vertical,1,METER_RET4R,dnp
J23,PinHeader_1x08_P2.54mm_Vertical,1,CV_IN,dnp
J24,PinHeader_1x02_P2.54mm_Vertical,1,METER_MIX_L,dnp
J25,PinHeader_1x02_P2.54mm_Vertical,1,METER_MIX_R,dnp
J3,IDC-Header_2x12_P2.54mm_Vertical,1,MASTER_IO,C53207829
J4,PinHeader_1x10_P2.54mm_Vertical,1,LCV_IN,dnp
J5,IDC-Header_2x12_P2.54mm_Vertical,1,AUX_IN,C53207829
J6,IDC-Header_2x12_P2.54mm_Vertical,1,AUX_OUT,C53207829
J7,PinHeader_1x03_P2.54mm_Vertical,1,PHONES,dnp
J73,IDC-Header_2x12_P2.54mm_Vertical,1,BUSES_IN_LEFT_CONNECTOR,C53207829
J74,IDC-Header_2x12_P2.54mm_Vertical,1,BUSES_IN_RIGHT_CONNECTOR,C53207829
J8,PinHeader_1x02_P2.54mm_Vertical,1,METER_AUX1L,dnp
J9,PinHeader_1x02_P2.54mm_Vertical,1,METER_AUX1R,dnp
"K1, K10, K11, K12, K13, K2, K3, K4, K5, K6, K7, K8, K9",Relay_DPDT_Omron_G6K-2F-Y,13,G6K-2F-Y DC12,C397194
Q1,SOT-23,1,2N7002,C8545
"R1, R103, R106, R11, R111, R113, R126, R128, R129, R131, R14, R19, R30, R33, R36, R41, R43, R56, R59, R64, R66, R80, R83, R88, R90",0603,25,4.99k 0.1%,C190614
"R10, R105, R112, R12, R127, R13, R130, R139, R140, R141, R142, R143, R144, R145, R146, R15, R151, R152, R153, R154, R155, R156, R157, R158, R16, R163, R166, R167, R168, R169, R173, R174, R179, R18, R21, R25, R26, R28, R29, R3, R31, R32, R35, R4, R42, R5, R58, R65, R82, R89",0603,50,10.0k 0.1%,C95204
"R100, R108, R123, R38, R53, R61, R76, R85",0603,8,2.37k 0.1%,C50670507
"R101, R109, R124, R39, R54, R62, R77, R86",0603,8,5.1k,C122969
"R102, R110, R125, R181, R182, R183, R184, R185, R186, R187, R188, R40, R55, R63, R78, R87",0603,16,100,C122970
"R104, R107, R116, R122, R34, R37, R46, R52, R57, R60, R69, R75, R81, R84, R93, R99",0603,16,20k 0.1%,C190611
"R114, R44, R67, R91",0603,4,267k 0.1%,C861785
"R115, R45, R68, R92",0603,4,28k 0.1%,C705756
"R117, R121, R133, R134, R189, R23, R47, R51, R70, R74, R8, R94, R98",0603,13,100k,C122538
"R118, R48, R71, R95",0805,4,164k 0.1%,C865214
"R119, R49, R72, R96",0603,4,37.9k 0.1%,C861362
"R120, R50, R73, R97",0603,4,51.1k 0.1%,C491138
"R132, R135, R136, R137, R138, R147, R148, R149, R150, R159, R160, R161, R162",1206,13,330,C17930
"R164, R165",0603,2,523 0.1%,C861461
"R17, R2, R24, R9",0603,4,4.70k 0.1%,C328429
"R170, R177",0603,2,1M,C234360
"R171, R176",0805,2,10,C136903
"R172, R175, R27",0603,3,2.49k 0.1%,C319797
"R178, R180",0603,2,4.7k 0.1%,C328429
"R20, R22, R6, R7",0603,4,20.0k 0.1%,C190611
R79,0603,1,56.2k,C23080
"TH1, TH2, TH3, TH4",R_Axial_DIN0207_L6.3mm_D2.5mm_P2.54mm_Vertical,4,NTC 47k,dnp
"U1, U2, U5, U6, U7",SOIC-8_3.9x4.9mm_P1.27mm,5,OPA1612,C94590
"U10, U21, U3, U4, U40, U41, U8",TSSOP-14_4.4x5mm_P0.65mm,7,OPA1679,C2057264
"U11, U16, U22, U26, U31",TSSOP-14_4.4x5mm_P0.65mm,5,INA1650,C553130
"U12, U17, U23, U27",TSSOP-16_4.4x5mm_P0.65mm,4,ADG1436,C408899
U13,SOIC-14_3.9x8.7mm_P1.27mm,1,OPA4197,C2058532
"U14, U15, U18, U20, U24, U25, U28, U9",PinSocket_1x08_P2.54mm_Vertical,8,AS2180,dnp
U19,SOT-23,1,ADR5041,C2686108
"U29, U30, U32, U33, U34, U35, U36, U37, U38, U39, U42, U44",SOIC-8_3.9x4.9mm_P1.27mm,12,DRV135,C544663
U43,Texas_S-PVSON-N10_ThermalVias,1,OPA1622,C2876559
